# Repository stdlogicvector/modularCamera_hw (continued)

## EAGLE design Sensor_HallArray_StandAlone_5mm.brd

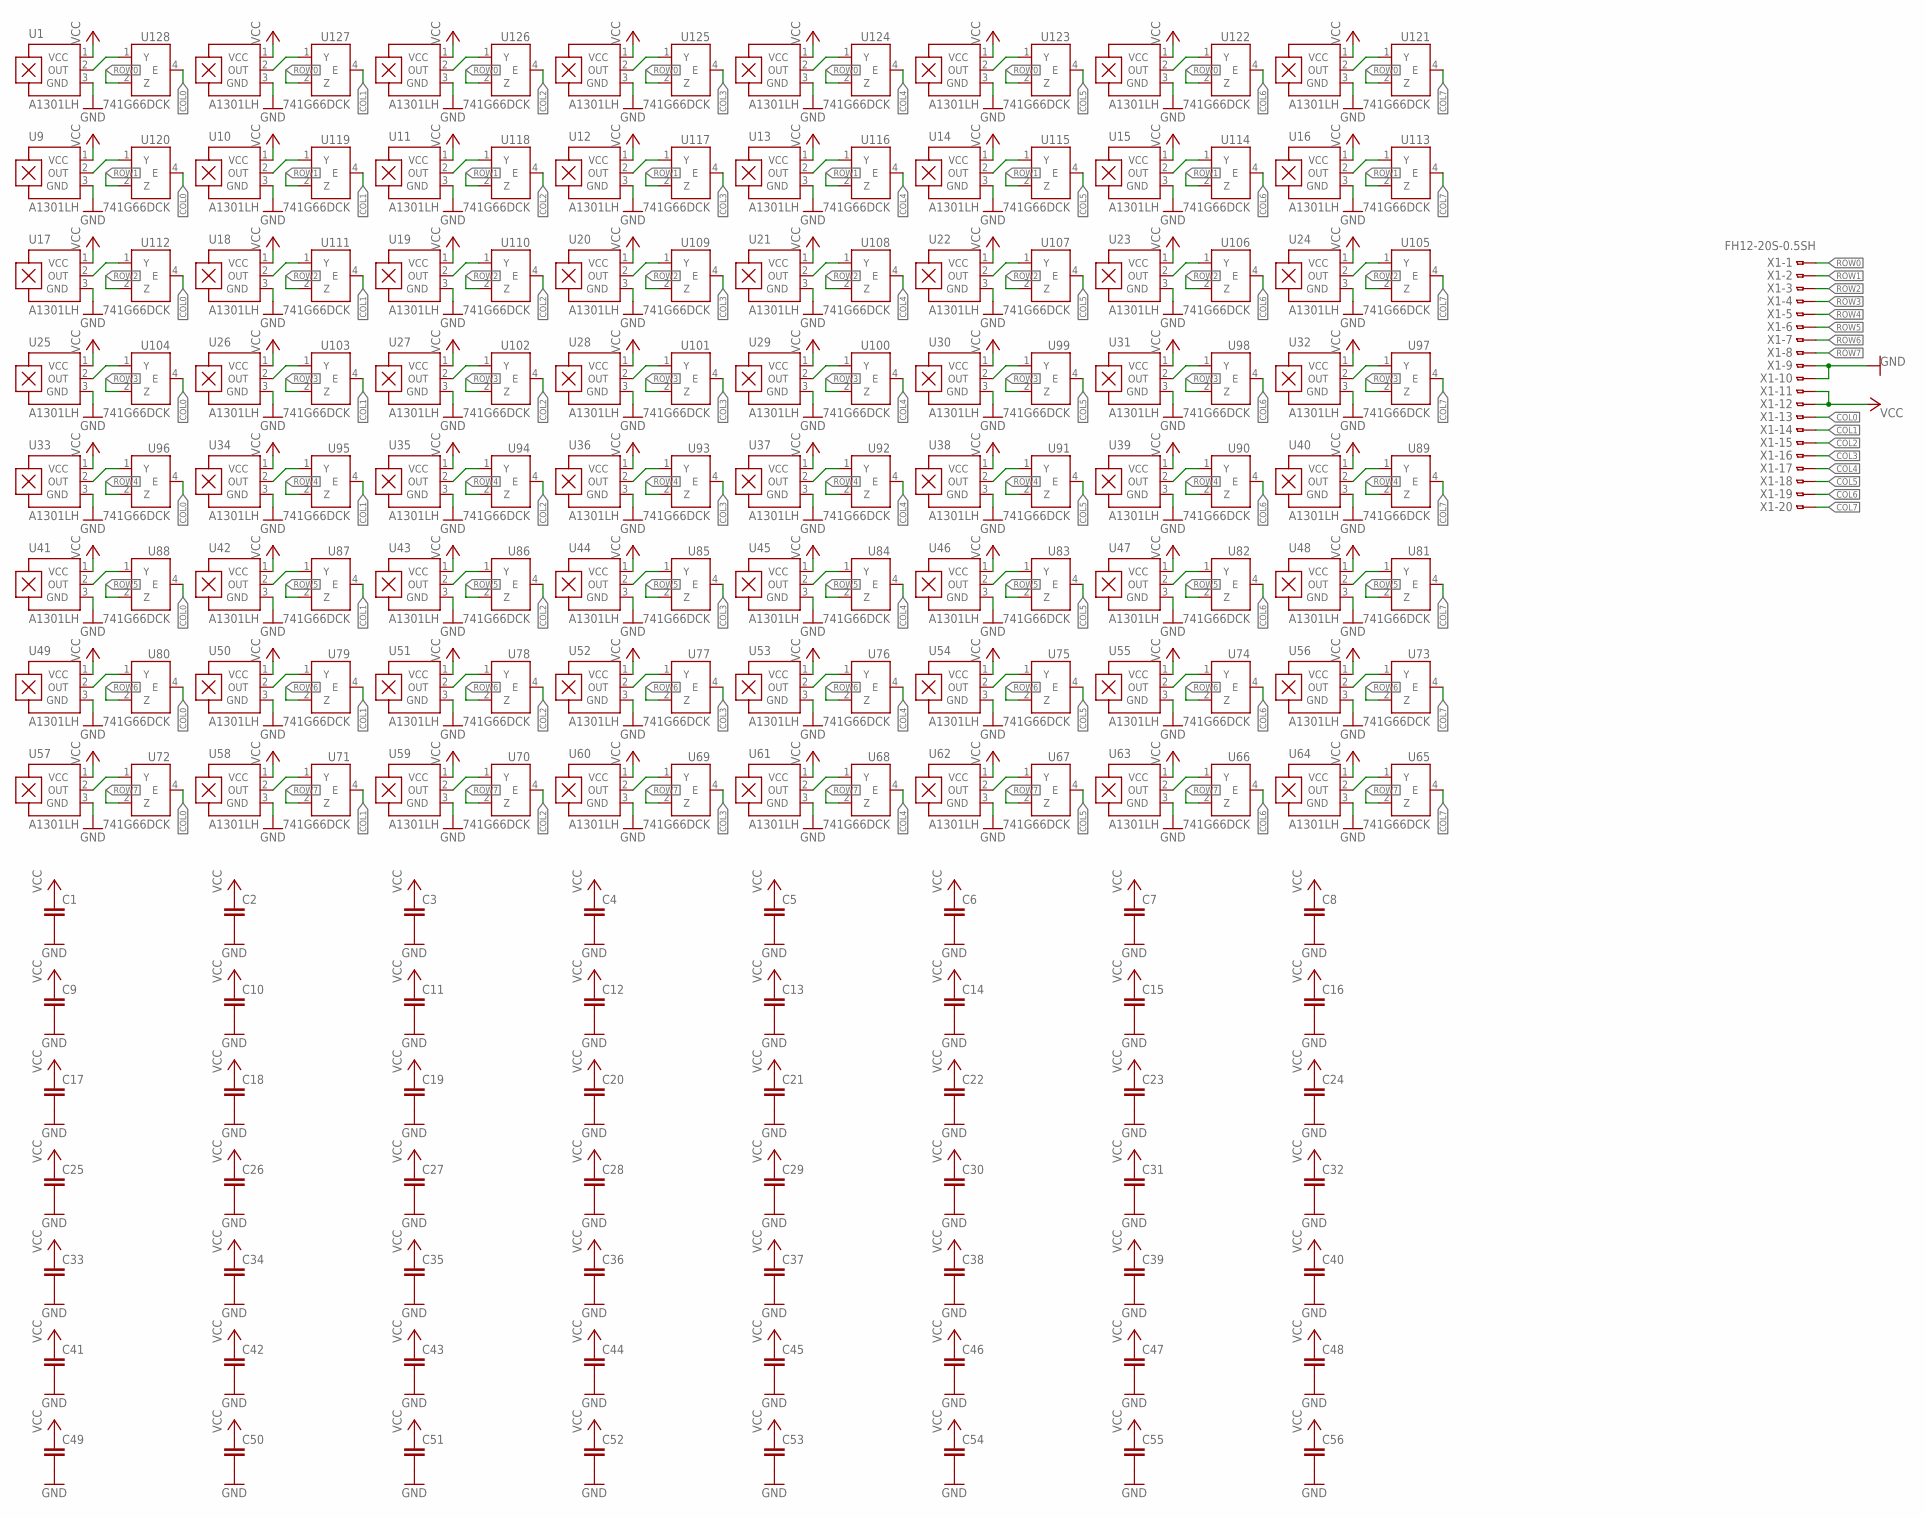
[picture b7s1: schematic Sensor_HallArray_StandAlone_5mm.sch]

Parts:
C1, C2, C3, C4, C5, C6, C7, C8, C9, C10, C11, C12, C13, C14, C15, C16, C17, C18, C19, C20, C21, C22, C23, C24, C25, C26, C27, C28, C29, C30, C31, C32, C33, C34, C35, C36, C37, C38, C39, C40, C41, C42, C43, C44, C45, C46, C47, C48, C49, C50, C51, C52, C53, C54, C55, C56: C-EUC0402; C0402
U1, U2, U3, U4, U5, U6, U7, U8, U9, U10, U11, U12, U13, U14, U15, U16, U17, U18, U19, U20, U21, U22, U23, U24, U25, U26, U27, U28, U29, U30, U31, U32, U33, U34, U35, U36, U37, U38, U39, U40, U41, U42, U43, U44, U45, U46, U47, U48, U49, U50, U51, U52, U53, U54, U55, U56, U57, U58, U59, U60, U61, U62, U63, U64: A1301LH; SOT23-W
U65, U66, U67, U68, U69, U70, U71, U72, U73, U74, U75, U76, U77, U78, U79, U80, U81, U82, U83, U84, U85, U86, U87, U88, U89, U90, U91, U92, U93, U94, U95, U96, U97, U98, U99, U100, U101, U102, U103, U104, U105, U106, U107, U108, U109, U110, U111, U112, U113, U114, U115, U116, U117, U118, U119, U120, U121, U122, U123, U124, U125, U126, U127, U128: 741G66DCK; SC70-5
X1: FH12-20S-0.5SH

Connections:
COL0: U72.4 (E), U80.4 (E), U88.4 (E), U96.4 (E), U104.4 (E), U112.4 (E), U120.4 (E), U128.4 (E), X1.13
COL1: U71.4 (E), U79.4 (E), U87.4 (E), U95.4 (E), U103.4 (E), U111.4 (E), U119.4 (E), U127.4 (E), X1.14
COL2: U70.4 (E), U78.4 (E), U86.4 (E), U94.4 (E), U102.4 (E), U110.4 (E), U118.4 (E), U126.4 (E), X1.15
COL3: U69.4 (E), U77.4 (E), U85.4 (E), U93.4 (E), U101.4 (E), U109.4 (E), U117.4 (E), U125.4 (E), X1.16
COL4: U68.4 (E), U76.4 (E), U84.4 (E), U92.4 (E), U100.4 (E), U108.4 (E), U116.4 (E), U124.4 (E), X1.17
COL5: U67.4 (E), U75.4 (E), U83.4 (E), U91.4 (E), U99.4 (E), U107.4 (E), U115.4 (E), U123.4 (E), X1.18
COL6: U66.4 (E), U74.4 (E), U82.4 (E), U90.4 (E), U98.4 (E), U106.4 (E), U114.4 (E), U122.4 (E), X1.19
COL7: U65.4 (E), U73.4 (E), U81.4 (E), U89.4 (E), U97.4 (E), U105.4 (E), U113.4 (E), U121.4 (E), X1.20
GND: C1.2, C2.2, C3.2, C4.2, C5.2, C6.2, C7.2, C8.2, C9.2, C10.2, C11.2, C12.2, C13.2, C14.2, C15.2, C16.2, C17.2, C18.2, C19.2, C20.2, C21.2, C22.2, C23.2, C24.2, C25.2, C26.2, C27.2, C28.2, C29.2, C30.2, C31.2, C32.2, C33.2, C34.2, C35.2, C36.2, C37.2, C38.2, C39.2, C40.2, C41.2, C42.2, C43.2, C44.2, C45.2, C46.2, C47.2, C48.2, C49.2, C50.2, C51.2, C52.2, C53.2, C54.2, C55.2, C56.2, U1.3 (GND), U2.3 (GND), U3.3 (GND), U4.3 (GND), U5.3 (GND), U6.3 (GND), U7.3 (GND), U8.3 (GND), U9.3 (GND), U10.3 (GND), U11.3 (GND), U12.3 (GND), U13.3 (GND), U14.3 (GND), U15.3 (GND), U16.3 (GND), U17.3 (GND), U18.3 (GND), U19.3 (GND), U20.3 (GND), U21.3 (GND), U22.3 (GND), U23.3 (GND), U24.3 (GND), U25.3 (GND), U26.3 (GND), U27.3 (GND), U28.3 (GND), U29.3 (GND), U30.3 (GND), U31.3 (GND), U32.3 (GND), U33.3 (GND), U34.3 (GND), U35.3 (GND), U36.3 (GND), U37.3 (GND), U38.3 (GND), U39.3 (GND), U40.3 (GND), U41.3 (GND), U42.3 (GND), U43.3 (GND), U44.3 (GND), U45.3 (GND), U46.3 (GND), U47.3 (GND), U48.3 (GND), U49.3 (GND), U50.3 (GND), U51.3 (GND), U52.3 (GND), U53.3 (GND), U54.3 (GND), U55.3 (GND), U56.3 (GND), U57.3 (GND), U58.3 (GND), U59.3 (GND), U60.3 (GND), U61.3 (GND), U62.3 (GND), U63.3 (GND), U64.3 (GND), U65.3 (GND), U66.3 (GND), U67.3 (GND), U68.3 (GND), U69.3 (GND), U70.3 (GND), U71.3 (GND), U72.3 (GND), U73.3 (GND), U74.3 (GND), U75.3 (GND), U76.3 (GND), U77.3 (GND), U78.3 (GND), U79.3 (GND), U80.3 (GND), U81.3 (GND), U82.3 (GND), U83.3 (GND), U84.3 (GND), U85.3 (GND), U86.3 (GND), U87.3 (GND), U88.3 (GND), U89.3 (GND), U90.3 (GND), U91.3 (GND), U92.3 (GND), U93.3 (GND), U94.3 (GND), U95.3 (GND), U96.3 (GND), U97.3 (GND), U98.3 (GND), U99.3 (GND), U100.3 (GND), U101.3 (GND), U102.3 (GND), U103.3 (GND), U104.3 (GND), U105.3 (GND), U106.3 (GND), U107.3 (GND), U108.3 (GND), U109.3 (GND), U110.3 (GND), U111.3 (GND), U112.3 (GND), U113.3 (GND), U114.3 (GND), U115.3 (GND), U116.3 (GND), U117.3 (GND), U118.3 (GND), U119.3 (GND), U120.3 (GND), U121.3 (GND), U122.3 (GND), U123.3 (GND), U124.3 (GND), U125.3 (GND), U126.3 (GND), U127.3 (GND), U128.3 (GND), X1.9, X1.10
unnamed: U1.2 (OUT), U128.1 (Y)
unnamed: U2.2 (OUT), U127.1 (Y)
unnamed: U9.2 (OUT), U120.1 (Y)
unnamed: U3.2 (OUT), U126.1 (Y)
unnamed: U4.2 (OUT), U125.1 (Y)
unnamed: U5.2 (OUT), U124.1 (Y)
unnamed: U6.2 (OUT), U123.1 (Y)
unnamed: U7.2 (OUT), U122.1 (Y)
unnamed: U8.2 (OUT), U121.1 (Y)
unnamed: U10.2 (OUT), U119.1 (Y)
unnamed: U11.2 (OUT), U118.1 (Y)
unnamed: U12.2 (OUT), U117.1 (Y)
unnamed: U13.2 (OUT), U116.1 (Y)
unnamed: U14.2 (OUT), U115.1 (Y)
unnamed: U15.2 (OUT), U114.1 (Y)
unnamed: U16.2 (OUT), U113.1 (Y)
unnamed: U17.2 (OUT), U112.1 (Y)
unnamed: U18.2 (OUT), U111.1 (Y)
unnamed: U19.2 (OUT), U110.1 (Y)
unnamed: U20.2 (OUT), U109.1 (Y)
unnamed: U21.2 (OUT), U108.1 (Y)
unnamed: U22.2 (OUT), U107.1 (Y)
unnamed: U23.2 (OUT), U106.1 (Y)
unnamed: U24.2 (OUT), U105.1 (Y)
unnamed: U25.2 (OUT), U104.1 (Y)
unnamed: U26.2 (OUT), U103.1 (Y)
unnamed: U27.2 (OUT), U102.1 (Y)
unnamed: U28.2 (OUT), U101.1 (Y)
unnamed: U29.2 (OUT), U100.1 (Y)
unnamed: U30.2 (OUT), U99.1 (Y)
unnamed: U31.2 (OUT), U98.1 (Y)
unnamed: U32.2 (OUT), U97.1 (Y)
unnamed: U33.2 (OUT), U96.1 (Y)
unnamed: U34.2 (OUT), U95.1 (Y)
unnamed: U35.2 (OUT), U94.1 (Y)
unnamed: U36.2 (OUT), U93.1 (Y)
unnamed: U37.2 (OUT), U92.1 (Y)
unnamed: U38.2 (OUT), U91.1 (Y)
unnamed: U39.2 (OUT), U90.1 (Y)
unnamed: U40.2 (OUT), U89.1 (Y)
unnamed: U41.2 (OUT), U88.1 (Y)
unnamed: U42.2 (OUT), U87.1 (Y)
unnamed: U43.2 (OUT), U86.1 (Y)
unnamed: U44.2 (OUT), U85.1 (Y)
unnamed: U45.2 (OUT), U84.1 (Y)
unnamed: U46.2 (OUT), U83.1 (Y)
unnamed: U47.2 (OUT), U82.1 (Y)
unnamed: U48.2 (OUT), U81.1 (Y)
unnamed: U49.2 (OUT), U80.1 (Y)
unnamed: U50.2 (OUT), U79.1 (Y)
unnamed: U51.2 (OUT), U78.1 (Y)
unnamed: U52.2 (OUT), U77.1 (Y)
unnamed: U53.2 (OUT), U76.1 (Y)
unnamed: U54.2 (OUT), U75.1 (Y)
unnamed: U55.2 (OUT), U74.1 (Y)
unnamed: U56.2 (OUT), U73.1 (Y)
unnamed: U57.2 (OUT), U72.1 (Y)
unnamed: U58.2 (OUT), U71.1 (Y)
unnamed: U59.2 (OUT), U70.1 (Y)
unnamed: U60.2 (OUT), U69.1 (Y)
unnamed: U61.2 (OUT), U68.1 (Y)
unnamed: U62.2 (OUT), U67.1 (Y)
unnamed: U63.2 (OUT), U66.1 (Y)
unnamed: U64.2 (OUT), U65.1 (Y)
ROW0: U121.2 (Z), U122.2 (Z), U123.2 (Z), U124.2 (Z), U125.2 (Z), U126.2 (Z), U127.2 (Z), U128.2 (Z), X1.1
ROW1: U113.2 (Z), U114.2 (Z), U115.2 (Z), U116.2 (Z), U117.2 (Z), U118.2 (Z), U119.2 (Z), U120.2 (Z), X1.2
ROW2: U105.2 (Z), U106.2 (Z), U107.2 (Z), U108.2 (Z), U109.2 (Z), U110.2 (Z), U111.2 (Z), U112.2 (Z), X1.3
ROW3: U97.2 (Z), U98.2 (Z), U99.2 (Z), U100.2 (Z), U101.2 (Z), U102.2 (Z), U103.2 (Z), U104.2 (Z), X1.4
ROW4: U89.2 (Z), U90.2 (Z), U91.2 (Z), U92.2 (Z), U93.2 (Z), U94.2 (Z), U95.2 (Z), U96.2 (Z), X1.5
ROW5: U81.2 (Z), U82.2 (Z), U83.2 (Z), U84.2 (Z), U85.2 (Z), U86.2 (Z), U87.2 (Z), U88.2 (Z), X1.6
ROW6: U73.2 (Z), U74.2 (Z), U75.2 (Z), U76.2 (Z), U77.2 (Z), U78.2 (Z), U79.2 (Z), U80.2 (Z), X1.7
ROW7: U65.2 (Z), U66.2 (Z), U67.2 (Z), U68.2 (Z), U69.2 (Z), U70.2 (Z), U71.2 (Z), U72.2 (Z), X1.8
VCC: C1.1, C2.1, C3.1, C4.1, C5.1, C6.1, C7.1, C8.1, C9.1, C10.1, C11.1, C12.1, C13.1, C14.1, C15.1, C16.1, C17.1, C18.1, C19.1, C20.1, C21.1, C22.1, C23.1, C24.1, C25.1, C26.1, C27.1, C28.1, C29.1, C30.1, C31.1, C32.1, C33.1, C34.1, C35.1, C36.1, C37.1, C38.1, C39.1, C40.1, C41.1, C42.1, C43.1, C44.1, C45.1, C46.1, C47.1, C48.1, C49.1, C50.1, C51.1, C52.1, C53.1, C54.1, C55.1, C56.1, U1.1 (VCC), U2.1 (VCC), U3.1 (VCC), U4.1 (VCC), U5.1 (VCC), U6.1 (VCC), U7.1 (VCC), U8.1 (VCC), U9.1 (VCC), U10.1 (VCC), U11.1 (VCC), U12.1 (VCC), U13.1 (VCC), U14.1 (VCC), U15.1 (VCC), U16.1 (VCC), U17.1 (VCC), U18.1 (VCC), U19.1 (VCC), U20.1 (VCC), U21.1 (VCC), U22.1 (VCC), U23.1 (VCC), U24.1 (VCC), U25.1 (VCC), U26.1 (VCC), U27.1 (VCC), U28.1 (VCC), U29.1 (VCC), U30.1 (VCC), U31.1 (VCC), U32.1 (VCC), U33.1 (VCC), U34.1 (VCC), U35.1 (VCC), U36.1 (VCC), U37.1 (VCC), U38.1 (VCC), U39.1 (VCC), U40.1 (VCC), U41.1 (VCC), U42.1 (VCC), U43.1 (VCC), U44.1 (VCC), U45.1 (VCC), U46.1 (VCC), U47.1 (VCC), U48.1 (VCC), U49.1 (VCC), U50.1 (VCC), U51.1 (VCC), U52.1 (VCC), U53.1 (VCC), U54.1 (VCC), U55.1 (VCC), U56.1 (VCC), U57.1 (VCC), U58.1 (VCC), U59.1 (VCC), U60.1 (VCC), U61.1 (VCC), U62.1 (VCC), U63.1 (VCC), U64.1 (VCC), U65.5 (VCC), U66.5 (VCC), U67.5 (VCC), U68.5 (VCC), U69.5 (VCC), U70.5 (VCC), U71.5 (VCC), U72.5 (VCC), U73.5 (VCC), U74.5 (VCC), U75.5 (VCC), U76.5 (VCC), U77.5 (VCC), U78.5 (VCC), U79.5 (VCC), U80.5 (VCC), U81.5 (VCC), U82.5 (VCC), U83.5 (VCC), U84.5 (VCC), U85.5 (VCC), U86.5 (VCC), U87.5 (VCC), U88.5 (VCC), U89.5 (VCC), U90.5 (VCC), U91.5 (VCC), U92.5 (VCC), U93.5 (VCC), U94.5 (VCC), U95.5 (VCC), U96.5 (VCC), U97.5 (VCC), U98.5 (VCC), U99.5 (VCC), U100.5 (VCC), U101.5 (VCC), U102.5 (VCC), U103.5 (VCC), U104.5 (VCC), U105.5 (VCC), U106.5 (VCC), U107.5 (VCC), U108.5 (VCC), U109.5 (VCC), U110.5 (VCC), U111.5 (VCC), U112.5 (VCC), U113.5 (VCC), U114.5 (VCC), U115.5 (VCC), U116.5 (VCC), U117.5 (VCC), U118.5 (VCC), U119.5 (VCC), U120.5 (VCC), U121.5 (VCC), U122.5 (VCC), U123.5 (VCC), U124.5 (VCC), U125.5 (VCC), U126.5 (VCC), U127.5 (VCC), U128.5 (VCC), X1.11, X1.12

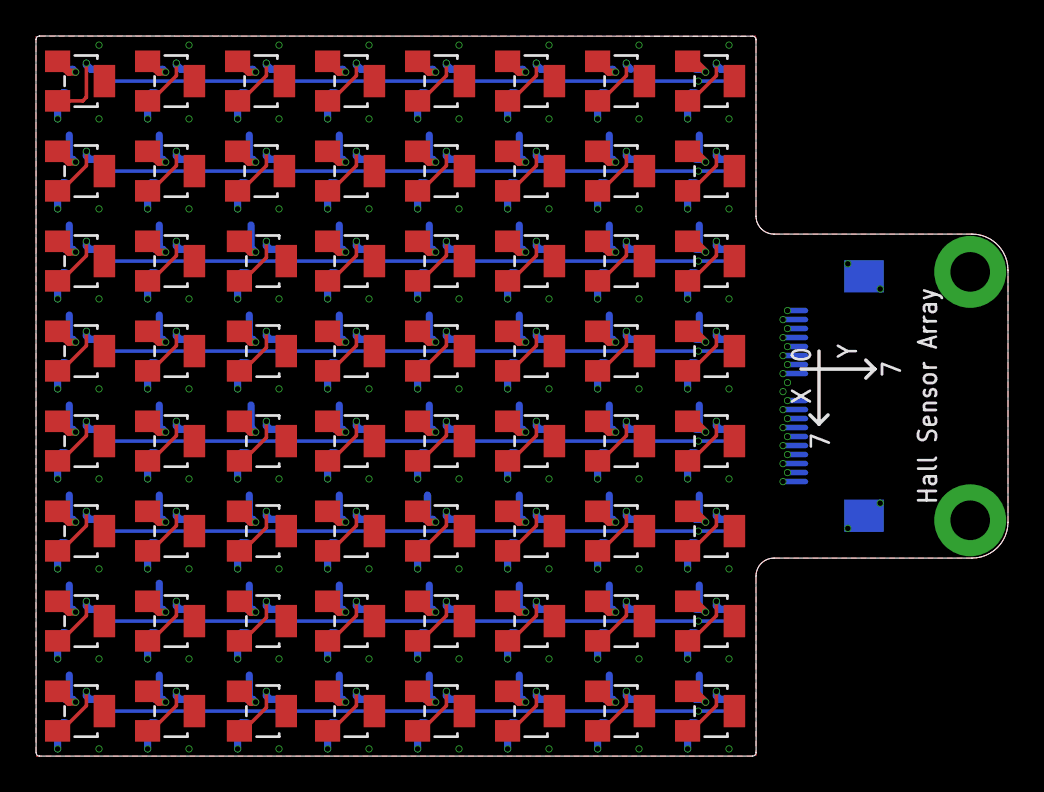
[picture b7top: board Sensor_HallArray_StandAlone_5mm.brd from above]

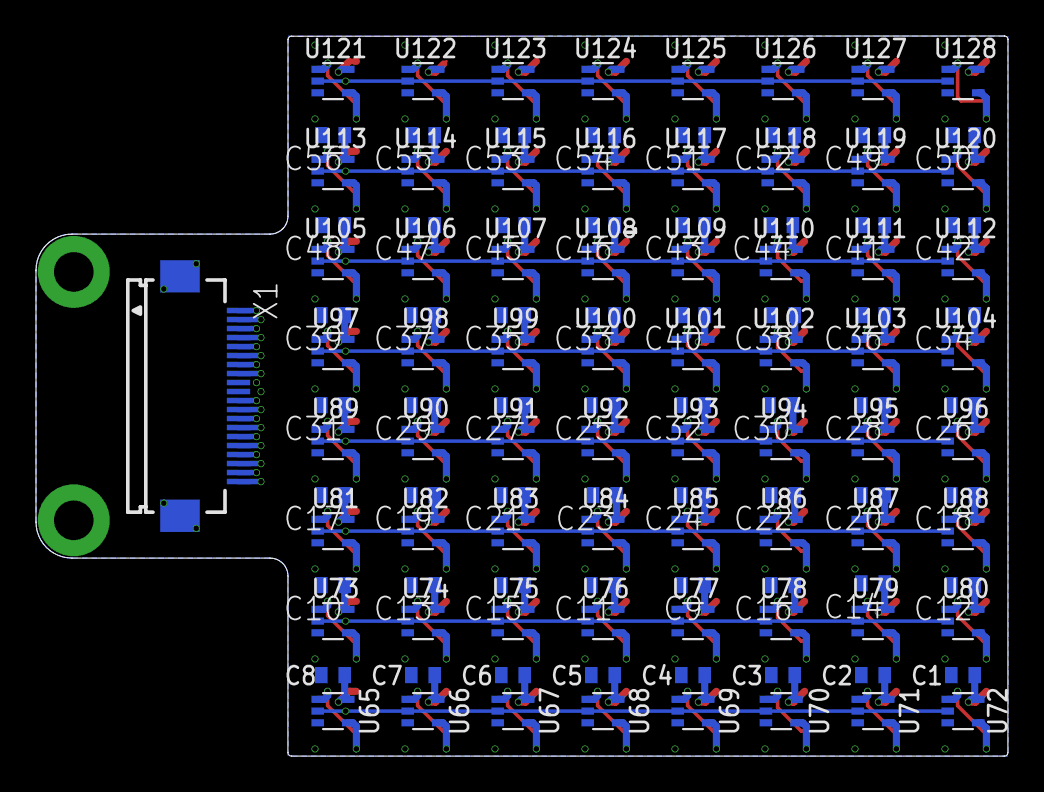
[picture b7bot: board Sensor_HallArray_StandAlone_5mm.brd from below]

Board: 4 copper layers, 54.0 x 40.0 mm, 185 parts (121 on the bottom side), 82 nets.

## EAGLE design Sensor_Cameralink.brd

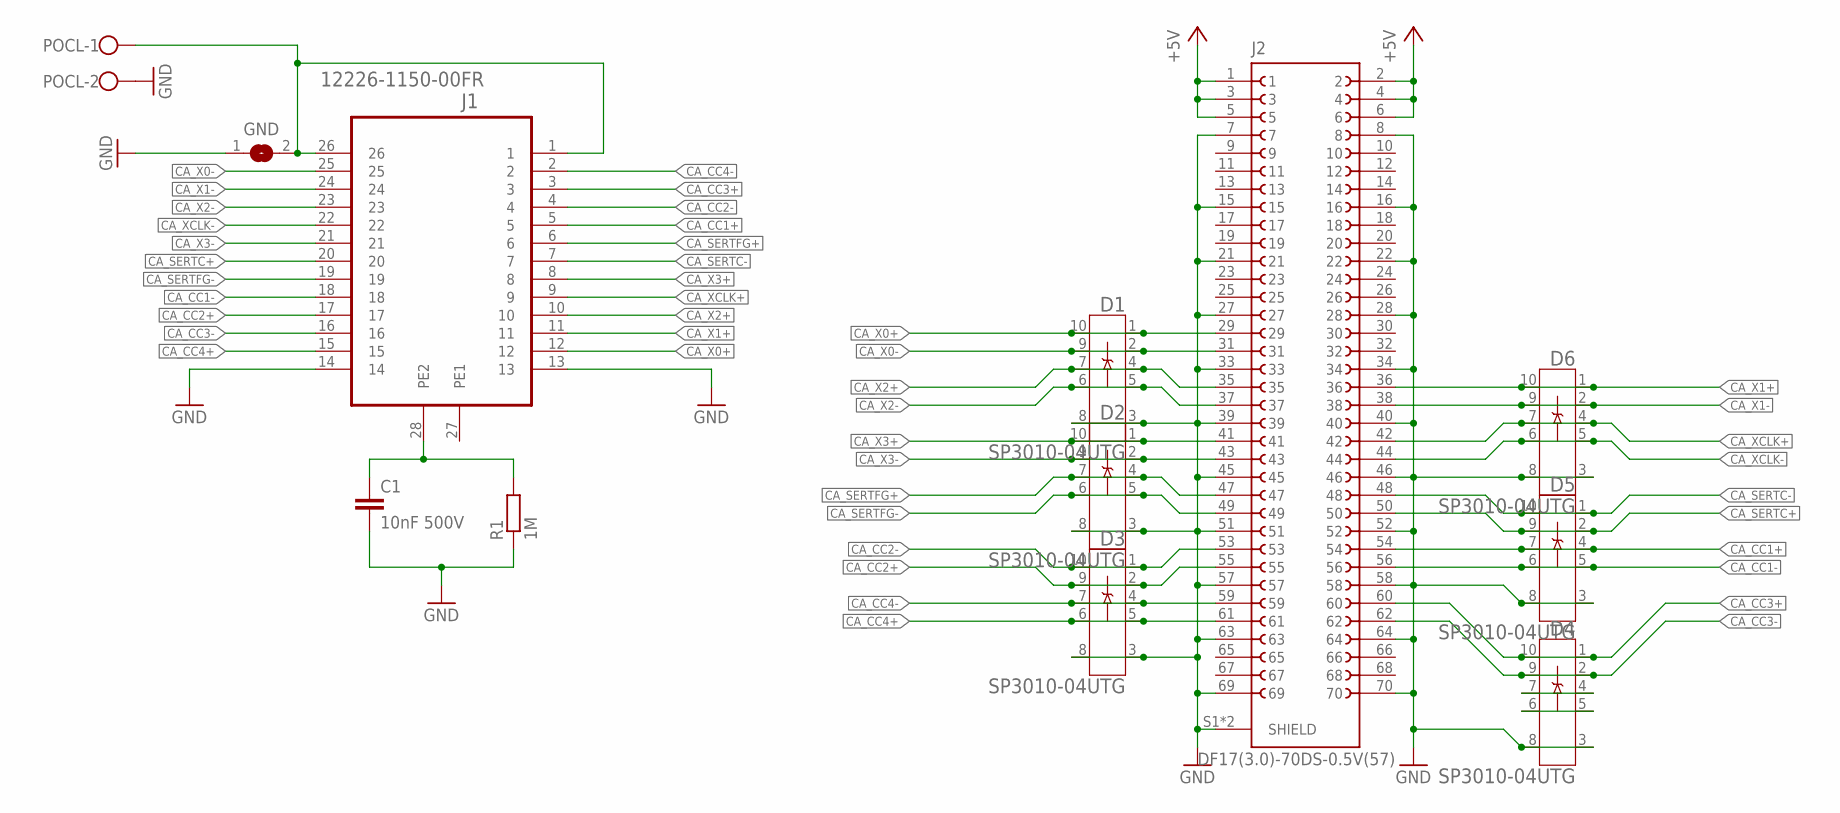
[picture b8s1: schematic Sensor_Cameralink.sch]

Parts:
C1: 10nF 500V; C0805
D1, D2, D3, D4, D5, D6: SP3010-04UTG; UDFEN-10_MO229_LTF; LCSC C126837
GND: SJ
J1: 12226-1150-00FR; 3M_12226-1150-00FR
J2: DF17(3.0)-70DS-0.5V(57)
POCL: W237-102
R1: 1M; R0805

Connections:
+5V: J2.1, J2.2, J2.3, J2.4, J2.5, J2.6
CA_CC1+: D5.4, D5.7, J1.5, J2.54
CA_CC1-: D5.5, D5.6, J1.18, J2.56
CA_CC2+: D3.2, D3.9, J1.17, J2.55
CA_CC2-: D3.1, D3.10, J1.4, J2.53
CA_CC3+: D4.1, D4.10, J1.3, J2.60
CA_CC3-: D4.2, D4.9, J1.16, J2.62
CA_CC4+: D3.5, D3.6, J1.15, J2.61
CA_CC4-: D3.4, D3.7, J1.2, J2.59
CA_SERTC+: D5.2, D5.9, J1.20, J2.50
CA_SERTC-: D5.1, D5.10, J1.7, J2.48
CA_SERTFG+: D2.4, D2.7, J1.6, J2.47
CA_SERTFG-: D2.5, D2.6, J1.19, J2.49
CA_X0+: D1.1, D1.10, J1.12, J2.29
CA_X0-: D1.2, D1.9, J1.25, J2.31
CA_X1+: D6.1, D6.10, J1.11, J2.36
CA_X1-: D6.2, D6.9, J1.24, J2.38
CA_X2+: D1.4, D1.7, J1.10, J2.35
CA_X2-: D1.5, D1.6, J1.23, J2.37
CA_X3+: D2.1, D2.10, J1.8, J2.41
CA_X3-: D2.2, D2.9, J1.21, J2.43
CA_XCLK+: D6.4, D6.7, J1.9, J2.42
CA_XCLK-: D6.5, D6.6, J1.22, J2.44
GND: C1.2, D1.3, D1.8, D2.3, D2.8, D3.3, D3.8, D4.3, D4.8, D5.3, D5.8, D6.3, D6.8, GND.1, J1.13, J1.14, J2.7, J2.8, J2.15, J2.16, J2.21, J2.22, J2.27, J2.28, J2.33, J2.34, J2.39, J2.40, J2.45, J2.46, J2.51, J2.52, J2.57, J2.58, J2.63, J2.64, J2.69, J2.70, J2.S1 (SHIELD), J2.S2 (SHIELD), POCL.2, R1.1
unnamed: D4.4, D4.7
unnamed: D4.5, D4.6
unnamed: C1.1, J1.28 (PE2), R1.2
unnamed: GND.2, J1.1, J1.26, POCL.1

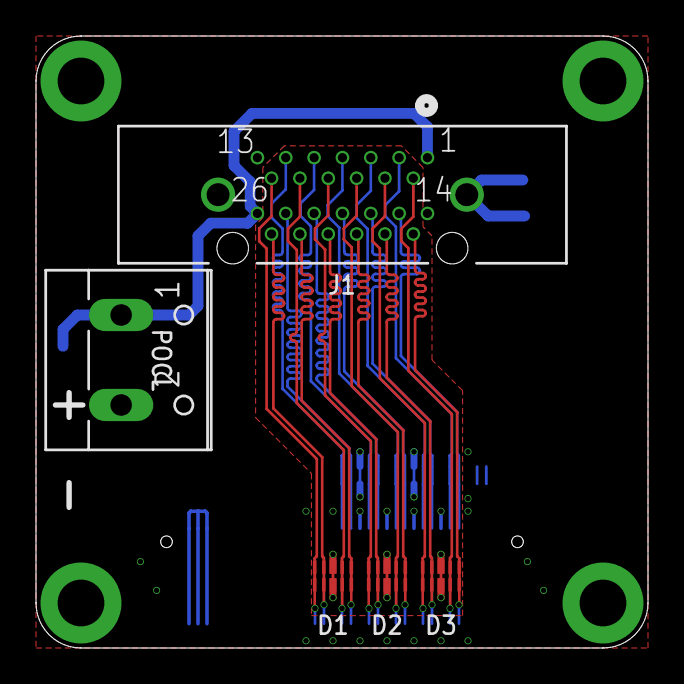
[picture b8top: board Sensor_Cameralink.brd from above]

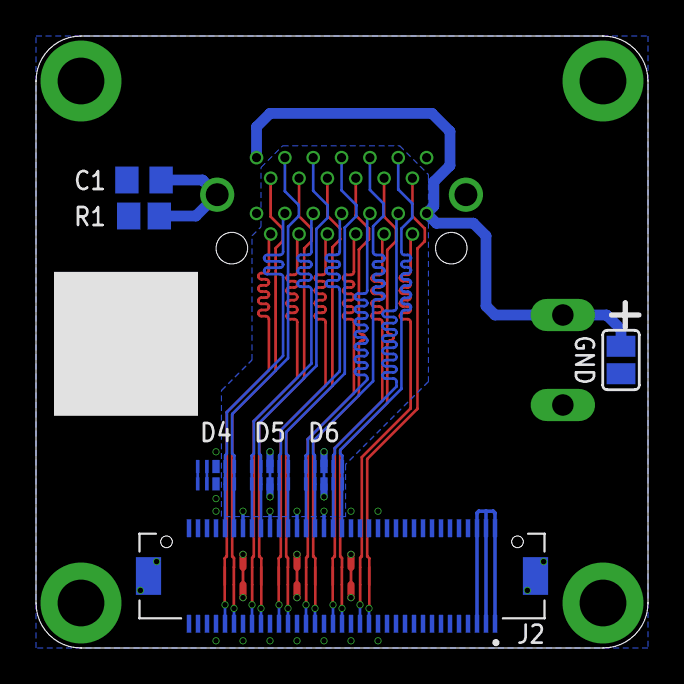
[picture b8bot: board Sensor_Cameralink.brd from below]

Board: 4 copper layers, 34.0 x 34.0 mm, 12 parts (7 on the bottom side), 28 nets.

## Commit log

2026-06-28 Add images
2026-06-28 Fix images
